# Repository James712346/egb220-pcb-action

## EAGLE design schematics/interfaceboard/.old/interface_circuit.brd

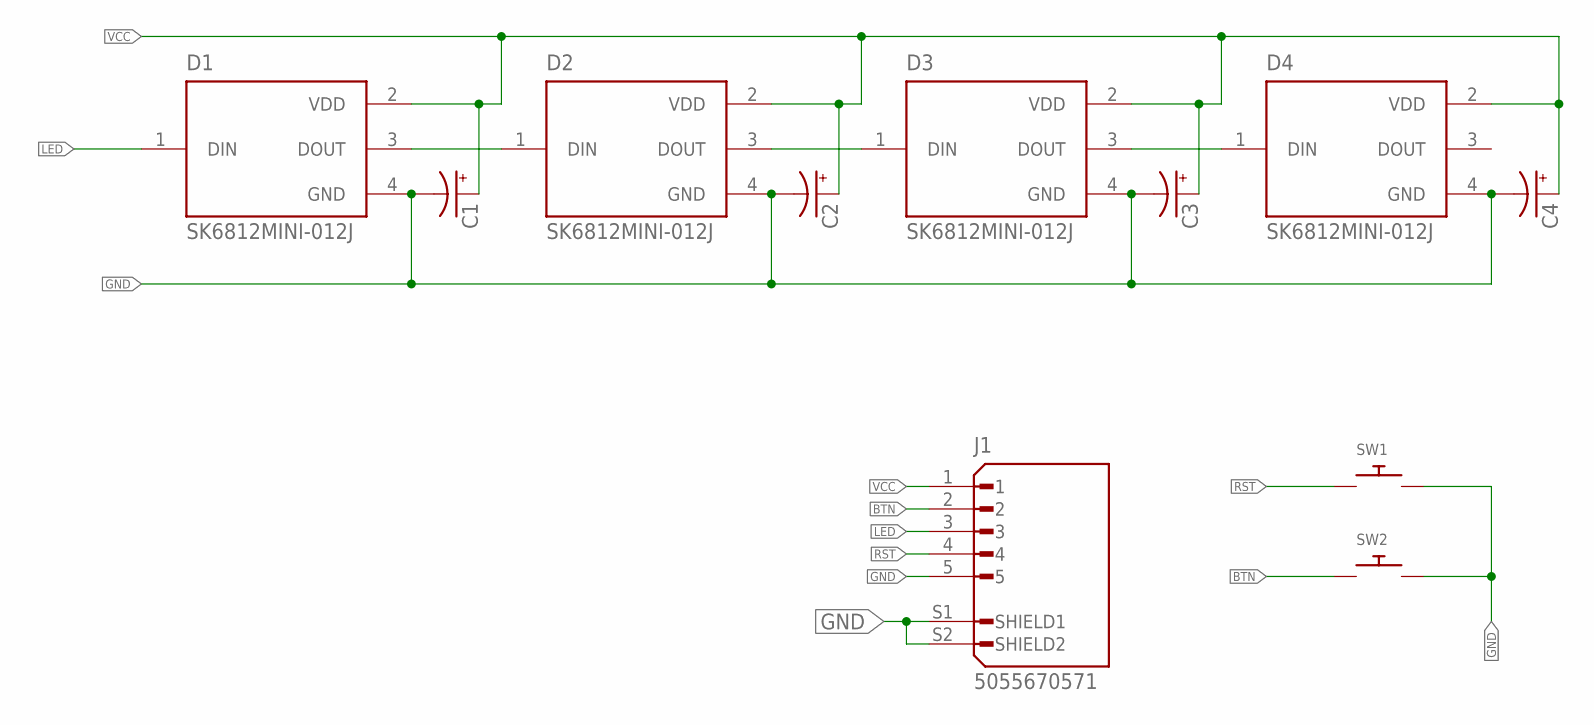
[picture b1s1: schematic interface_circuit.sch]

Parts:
C1, C2, C3, C4: CAP_POL1206; EIA3216
D1, D2, D3, D4: SK6812MINI-012J; LED_SK6812MINI-012
J1: 5055670571; MOLEX_5055670571
SW1, SW2: SWITCH_PUSHBUTTONSOFTTOUCHSMD_SJ; PUSHBUTTON_SMD_SJ

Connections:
BTN: J1.2, SW2.P$1
GND: C1.C (-), C2.C (-), C3.C (-), C4.C (-), D1.4 (GND), D2.4 (GND), D3.4 (GND), D4.4 (GND), J1.5, J1.S1 (SHIELD1), J1.S2 (SHIELD2), SW1.P$2, SW2.P$2
LED: D1.1 (DIN), J1.3
unnamed: D1.3 (DOUT), D2.1 (DIN)
unnamed: D2.3 (DOUT), D3.1 (DIN)
unnamed: D3.3 (DOUT), D4.1 (DIN)
RST: J1.4, SW1.P$1
VCC: C1.A (+), C2.A (+), C3.A (+), C4.A (+), D1.2 (VDD), D2.2 (VDD), D3.2 (VDD), D4.2 (VDD), J1.1

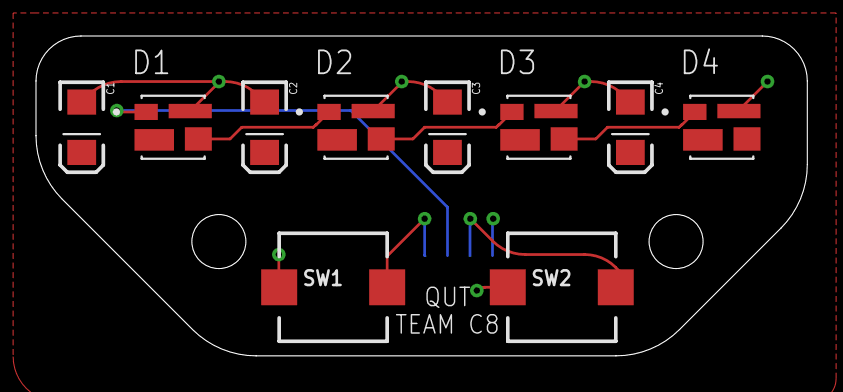
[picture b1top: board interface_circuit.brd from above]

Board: 2 copper layers, 42.8 x 17.8 mm, 11 parts (1 on the bottom side), 8 nets.

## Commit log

2024-04-18 Cating the package.txt
2024-04-18 Output text file
2024-04-18 Settings Tess dpi
2024-04-18 Trying a higher dpi
2024-04-18 setting dpi to limit
2024-04-18 Try 1000 dpi
2024-04-18 Copol
2024-04-18 Try this with set oem and psm
2024-04-18 oem 0
2024-04-23 Trying new git action
2024-04-23 forgot test cases
2024-04-23 Jq to list folders
2024-04-23 set output
2024-04-23 updated setting of values, and added captuire all
2024-04-23 setting up files correctly
2024-04-23 Focusing on librepcb atm
2024-04-23 Forgot to build them
2024-04-23 removing /tmp/
2024-04-23 newer version of librePCB
2024-04-23 Fixed version
2024-04-23 curious
2024-04-23 removed sudo
2024-04-23 debugging listing of gerber
2024-04-24 Forgot to change output step id
2024-04-24 maybe quotation
2024-04-24 forgot $
2024-04-24 Attempt at downloading all artifacts
2024-04-24 forgot to include file in the env
2024-04-25 Print all profiles
2024-04-25 sudo needed
2024-04-25 Fixed Empty strag
2024-04-25 debugging time :)
2024-04-25 Lets try echo print statments
2024-04-25 adding Pricing
2024-04-25 adding png lib
2024-04-25 try 2
2024-04-25 its the god dam image variable aaahhhh
2024-04-25 Added more indepth Sizing and calculations
2024-04-25 seperate the file names
2024-04-25 adding json component
2024-04-25 removed ID
2024-04-25 adding image pushing and processing
2024-04-25 attempt to fix json
2024-04-25 change key format
2024-04-25 forgot to push this too :0
2024-04-25 Echo lists
2024-04-25 Fixed list if statment
2024-04-25 attempting to get kicad execption passes
2024-04-25 Trying to get that if statment to call now
2024-04-25 workout why
2024-04-25 checkout is broken atm, lets first see if i can not ru kicad
2024-04-25 on to github checkout error yay
2024-04-25 too good, fixed on the first commit
2024-04-25 add keys to images
2024-04-25 see if my custom one works
2024-04-25 try new release
2024-04-25 Remove old actions
2024-04-25 its not getting the latest release
2024-04-25 yolo
2024-04-25 trying the old way
2024-04-25 added release job
2024-04-25 removed whitespace between eqeual on line one of generate readme
2024-04-25 Echo out all the json files
2024-04-25 Fixed Jq error, and few other items
2024-04-25 fixed up a few errors
2024-04-25 Zip up gerber files, and added json string
2024-04-25 Spelt gerber wrong
2024-04-25 trying to get jq to return the correct values
2024-04-25 escape the pricing
2024-04-25 echo silkscreen urls
2024-04-25 added tables
2024-04-25 stripped the image variable
2024-04-25 time to look at extracted text
2024-04-25 Fixing extract text
2024-04-25 Adding EOF to file
2024-04-25 new line might help
2024-04-25 try getting rid of \n in extracted text
2024-04-26 just printing extracted text
2024-04-26 Needed to escape the code ticks, as they are handled like quotes
2024-04-26 No longer need to remove /r and /n
2024-04-26 Adding bottom silk layer
2024-04-26 trying to add a new job
2024-04-26 Format Project
2024-04-26 try this
2024-04-26 get board on it own
2024-04-26 Adding EGB220 Checks
2024-04-26 Get Board works
2024-04-26 attempt 1, setting to string
2024-04-26 trying to get it to loop
2024-04-26 forgot to stage echo
2024-04-26 I feel so stupid
2024-04-26 this should work
2024-04-26 attempt 2
2024-04-26 debugging time
2024-04-26 This should fix the board looping issue
2024-04-26 add better team check, and added None flag
2024-04-26 remove exit
2024-04-26 adding some echos
2024-04-26 seperatating code
2024-04-26 grep causing a exit 1, so perl will be used instead
2024-04-26 Final Fixes
2024-04-26 Adding Global env
2024-04-26 Better Packaging Logic
2024-04-26 change of axis
2024-04-26 Fixed up a few packaging issues and added echo of project and boardname
2024-04-26 Fixed naming issue in package (Hopefully)
2024-04-27 attempting kicad
2024-04-27 New PCB
2024-04-27 xhwxk if it exists
2024-04-27 Try cd into project file
2024-04-27 realised kibot is inside a docker container
2024-04-27 using $(pwd) instead of .
2024-04-27 silly forgot about cat cmd
2024-04-27 changed to .
2024-04-27 fix up config
2024-04-27 setting up artifact
2024-04-27 setting dir
2024-04-27 try again without .
2024-04-27 added * to try and remove archieve tree
2024-04-27 archieving myself
2024-04-27 cd instead
2024-04-27 mv it outside working dir
2024-04-27 sudo that bitch
2024-04-27 YOLO complete directory
2024-04-27 Removed the rm .
2024-04-27 Update pcb.yml
    New tree
2024-04-27 Update pcb.yml
    I not sure why, but let's see
2024-04-28 try this to package -NPTH file with boardname
2024-04-28 add .drl to the exclude line for boardname
2024-04-28 lowering the case of all file names
2024-05-14 added outputs

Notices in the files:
parts and their libraries:
SparkFun: Licensing: CC v3.0 Share-Alike You are welcome to use this library for commercial purposes.
